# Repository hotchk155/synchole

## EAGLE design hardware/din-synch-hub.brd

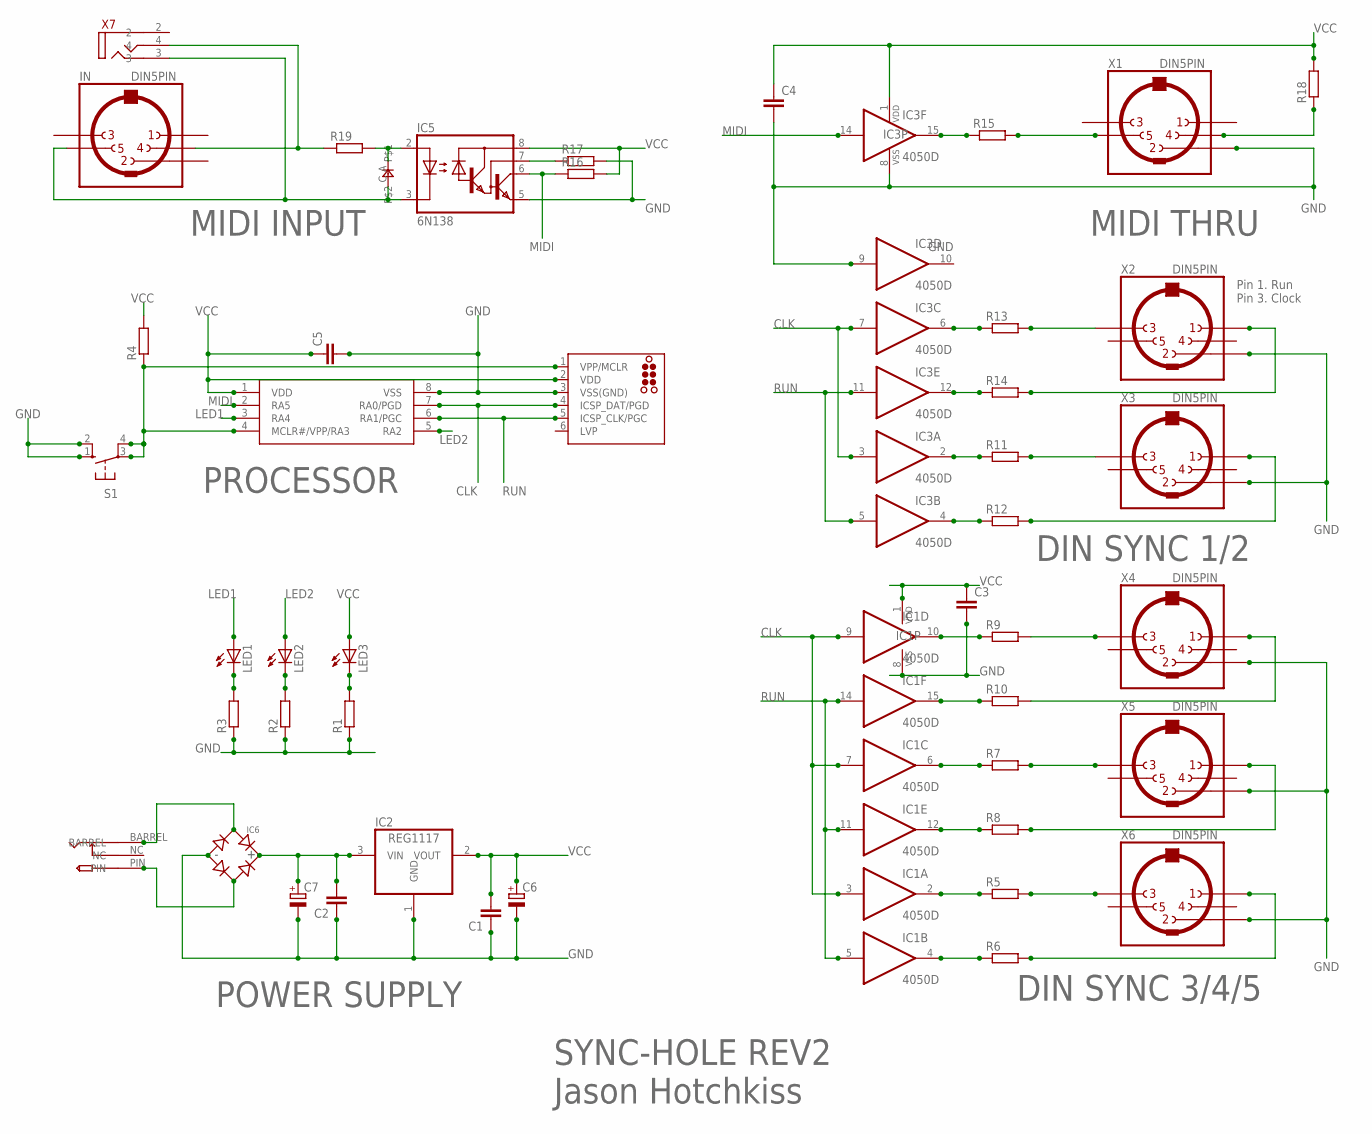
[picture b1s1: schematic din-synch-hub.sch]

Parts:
C1, C2, C3, C4, C5: C-EUC0805; C0805
C6, C7: CPOL-EUE2,5-6E; E2,5-6E
D1: 0805DIODE
IC1, IC3: 4050D; SO16
IC2: REG1117; SOT223
IC4: PIC12F1822SO08; SO08
IC5: 6N138; DIL08
IC6: BRIDGERECTIFIER; SOIC-4
ICSP: TC2030-MCP-NL
IN: DIN5PIN; EDGEDIN
LED1, LED2, LED3: LED3MM
R1, R2, R3, R4, R5, R6, R7, R8, R9, R10, R11, R12, R13, R14, R15, R16, R17, R18, R19: R-EU_R0805; R0805
S1: 10-XX; B3F-10XX
U$1: PWR_SOCKET_2_1MM
X1, X2, X3, X4, X5, X6: DIN5PIN; EDGEDIN
X7: VERTICAL_3_5MM_SOCKET

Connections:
CLK: IC1.3 (I), IC1.7 (I), IC1.9 (I), IC3.3 (I), IC3.7 (I), IC4.7 (RA0/PGD), ICSP.4 (ICSP_DAT/PGD)
GND: C1.1, C2.1, C3.2, C4.2, C5.2, C6.-, C7.-, IC1.8 (VSS), IC2.1 (GND), IC3.8 (VSS), IC3.9 (I), IC4.8 (VSS), IC5.5 (GND), IC6.-, ICSP.3 (VSS(GND)), R1.1, R2.1, R3.1, R17.2, S1.1 (S), S1.2 (S1), X1.2, X2.2, X3.2, X4.2, X5.2, X6.2
LED1: IC4.3 (RA4), LED1.A
LED2: IC4.5 (RA2), LED2.A
MIDI: IC3.14 (I), IC4.2 (RA5), IC5.6 (VO), R16.1
unnamed: IC3.15 (O), R15.1
unnamed: R15.2, X1.5
unnamed: IC3.6 (O), R13.1
unnamed: R18.1, X1.4
unnamed: IC3.12 (O), R14.1
unnamed: R13.2, X2.3
unnamed: IC3.4 (O), R12.1
unnamed: R14.2, X2.1
unnamed: IC3.2 (O), R11.1
unnamed: R11.2, X3.3
unnamed: R12.2, X3.1
unnamed: IC1.15 (O), R10.1
unnamed: IC1.12 (O), R8.1
unnamed: R9.2, X4.3
unnamed: IC1.10 (O), R9.1
unnamed: R10.2, X4.1
unnamed: IC1.2 (O), R5.1
unnamed: R7.2, X5.3
unnamed: IC1.4 (O), R6.1
unnamed: R8.2, X5.1
unnamed: IC1.6 (O), R7.1
unnamed: R5.2, X6.3
unnamed: R6.2, X6.1
unnamed: D1.C, IC5.3 (C), IN.5, X7.3
unnamed: IN.4, R19.1, X7.4
unnamed: D1.A, IC5.2 (A), R19.2
unnamed: LED3.K (C), R1.2
unnamed: IC5.7 (VB), R17.1
unnamed: IC4.4 (MCLR#/VPP/RA3), ICSP.1 (VPP/MCLR), R4.1, S1.3, S1.4 (P1)
unnamed: LED2.K (C), R2.2
unnamed: C2.2, C7.+, IC2.3 (VIN), IC6.+
unnamed: LED1.K (C), R3.2
unnamed: IC6.~2 (AC2), U$1.PIN
unnamed: IC6.~1 (AC1), U$1.BARREL
RUN: IC1.5 (I), IC1.11 (I), IC1.14 (I), IC3.5 (I), IC3.11 (I), IC4.6 (RA1/PGC), ICSP.5 (ICSP_CLK/PGC)
VCC: C1.2, C3.1, C4.1, C5.1, C6.+, IC1.1 (VDD), IC2.2 (VOUT), IC3.1 (VDD), IC4.1 (VDD), IC5.8 (VCC), ICSP.2 (VDD), LED3.A, R4.2, R16.2, R18.2

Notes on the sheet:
MIDI INPUT
PROCESSOR
POWER SUPPLY
MIDI THRU
DIN SYNC 1/2
DIN SYNC 3/4/5
SYNC-HOLE REV2
Jason Hotchkiss
Pin 1. Run Pin 3. Clock

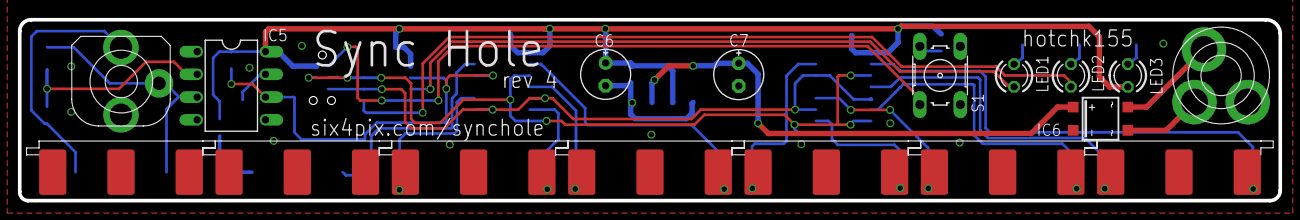
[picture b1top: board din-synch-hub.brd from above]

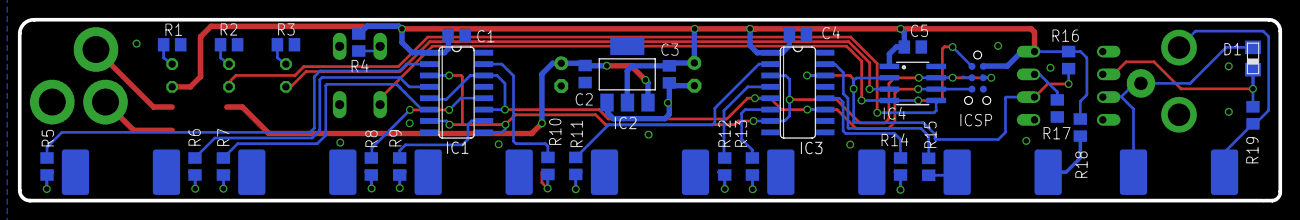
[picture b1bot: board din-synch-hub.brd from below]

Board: 2 copper layers, 140.7 x 20.2 mm, 47 parts (30 on the bottom side), 41 nets.

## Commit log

2015-10-04 stuff
2015-10-12 ready for fab
2015-11-19 version 1.0 of firmware
2016-02-05 case upodate
2016-02-14 case moved to new project
2016-02-14 v2 new PCB
2016-06-13 added new power socket
2016-06-13 major changes
2016-06-13 REV3
2016-06-13 final tweak to rev3?
2016-06-13 fix bug
2016-07-08 REV4
    moved leds to match bsplit
2016-07-08 move switch (rev4 pcb)
2025-12-12 PCB Fascia
2026-01-13 production files
2026-01-13 kicad project for front panel
2026-01-22 update packing slip

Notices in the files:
parts and their libraries:
tag-connect: ©2009 ROFA.cz - modified and updated by Robert Darlington ‹rdarlington@gmail.com›
